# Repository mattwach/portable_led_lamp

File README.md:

# Portable LED Lamp

*The page https://www.instructables.com/Portable-LED-Lamp and [pdf file](Portable-LED-Lamp.pdf)
contain detailed build instructions, a prebuilt firmware (`led_lamp.hex`) file
and prerendered `.stl` files.  The rest of the instructions on this page give
some additional details on the project and to explain how to build your own firmware.*

If you need light but don't have an outlet available, it's nice to have an
efficient light that can accept a wide variety of batteries.

This lamp can accept a wide range of voltages - between 6 and 30V. This allows
it to be **used with different batteries you may have lying around**, including
18650 packs, RC batteries, 12V lead acid, etc.

The unit is designed to be **very efficient** and puts out very little heat, even
at full power. A dimmer knob can be used to adjust the power consumption and
light output. When "off" the lamp consumes less than 40 uA of power in its
"sleep" state.

**Voltage and current are monitored on a small OLED display**. This allows you to
estimate battery life at a given light level and make adjustments as needed for
your situation.

The device has **automatic shutoff when the battery voltage gets too low**.

The device can autodetect the battery you are using with options for manual
override.

Before we get too far, a **disclaimer**:

**Using batteries carries a risk**. Making mistakes can lead to batteries catching
on fire. Sometimes batteries catch on fire even when everything is done
correctly due to unknown issues during manufacturing or shipping. It is
expected that you understand the risks associated with the battery you choose.
Even though the hardware and software in on this page have been tested, you
should not assume that your build and batteries will operate without problems.
I take no responsibility for issues you may encounter while following this
guide or using the provided software. Using a safety container for your battery
is recommended.

# Project Overview

This project contains:

  * Firmware in the `firmware/` directory.  This firmware is intended for the
    ATMega328p running at 3.3v and 8Mhz.  A 3.3V Arduino Pro Mini meets these specs
  * A [KiCad](https://www.kicad.org/) schematic and PCB layout in the
    `schematic/` directory
  * An [OpenSCAD](https://openscad.org/) 3D printable enclosure in the
    `3d_print/` directory.

# Schematics and Images

You'll want the free KiCAD tool to work on the schematics.  The images below are
screen captures from KiCAD for quick reference.

#### Master Board Schematic

#### Input Board Schematic

# Building the firmware

You will need the following commandline tools available.  All are free tools.
Getting them will vary depending on your operating system.

  * `avr-gcc`
  * `avr-objcopy`
  * `avrdude`

To build you run

    make

from the `firmware/` directory.  To upload to a ATMega328p (pro mini) you run

    make upload

Note that upload is currently not setup for windows, although it could be made
to work with a few tweaks to the relatively-simple `rules.mak` file.  The main
issue is likely to be incorrect `avrdude` parameters.  See the main `avrdude`
documentation for for more information.

# Enclosure (using OpenSCAD)

The file `3d_print/led_lamp.scad` contains the 3D models.

At the bottom of the file is a section:

    placed_master_pcb();
    placed_input_pcb();
    placed_picobuck_mount_plate(add_picobucks=true);
    placed_barrel_connector();
    lamp_base();
    placed_led_dome(show_leds=true, barrel_connector_cutout=true);
    input_holder();
    placed_dimmer_knob();

You can place a `*` character or comment out a line with a `//` to omit the
part.  You can also prefix a line with `!` to only show that part.  This is
useful for isolating a part for making a `.stl` model for printing.

# Design Notes

In have [design notes](DESIGN_NOTES.md) where I share test results for LED
efficiency, component power usage and other considerations.

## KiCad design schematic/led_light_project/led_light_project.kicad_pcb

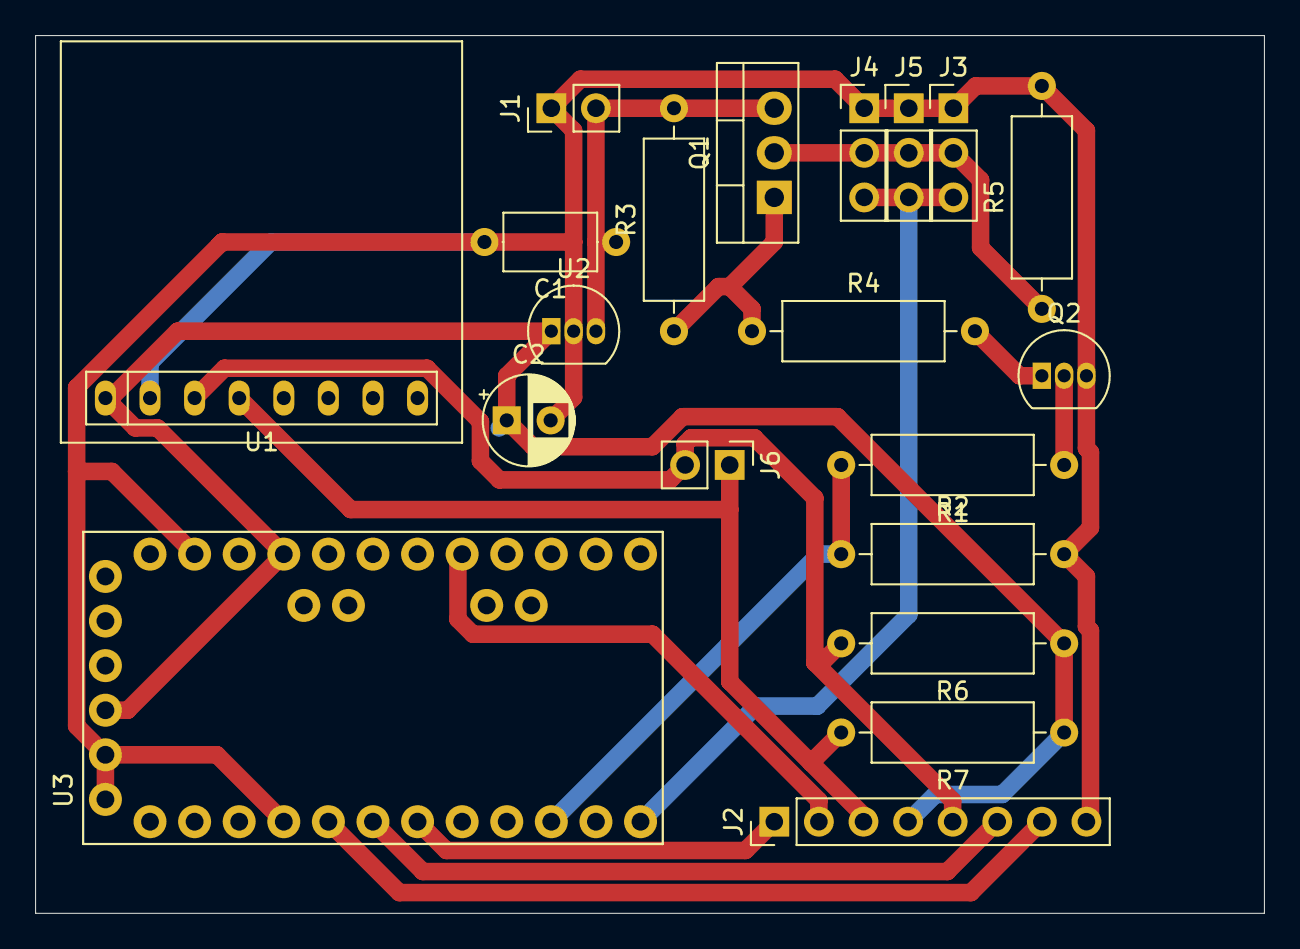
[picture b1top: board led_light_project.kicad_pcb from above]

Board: 2 copper layers, 70.0 x 50.0 mm, 20 parts (0 on the bottom side), 15 nets.

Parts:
C1: 100n; C_Axial_L5.1mm_D3.1mm_P7.50mm_Horizontal
C2: 10u; CP_Radial_D5.0mm_P2.50mm
J1: PWR_IN; PinHeader_1x02_P2.54mm_Vertical
J2: control_board_conn; PinHeader_1x08_P2.54mm_Vertical
J3: PICO_BUCK1; PinHeader_1x03_P2.54mm_Vertical
J4: PICO_BUCK2; PinHeader_1x03_P2.54mm_Vertical
J5: PICO_BUCK3; PinHeader_1x03_P2.54mm_Vertical
J6: I2C_Hookup; PinHeader_1x02_P2.54mm_Vertical
Q1: FQP27P06; TO-220-3_Vertical
Q2: BS170; TO-92_Inline
R1: 1k; R_Axial_DIN0309_L9.0mm_D3.2mm_P12.70mm_Horizontal
R2, R3, R5: 47k; R_Axial_DIN0309_L9.0mm_D3.2mm_P12.70mm_Horizontal
R4: 10k; R_Axial_DIN0309_L9.0mm_D3.2mm_P12.70mm_Horizontal
R6, R7: 4.7k; R_Axial_DIN0309_L9.0mm_D3.2mm_P12.70mm_Horizontal
U1: INA260; Adadruit_INA260_Breakout_Board
U2: LM2936-3.3_TO92; TO-92_Inline
U3: ARDUINO_PRO_MINI; MODULE_ARDUINO_PRO_MINI

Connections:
+3V3: C2.1, J2.4, R6.1, R7.1, U1.10, U2.1, U3.JP1_4, U3.JP6_4
+28V: C1.1, J1.2, Q1.3, R3.2, U2.3
/GREEN_BUT: J2.6, U3.JP7_7
/LED_ON: R1.2, R2.1, U3.JP7_3
/LED_VCC: J3.2, J4.2, J5.2, Q1.2, R5.1
/POTIN: J2.2, U3.JP6_8
/POT_VCC: J2.1, U3.JP7_6
/PWM: J3.3, J4.3, J5.3, U3.JP7_1
/RED_BUT: J2.7, U3.JP7_8
/SCL: J2.5, J6.2, R6.2, U1.9
/SDA: J2.3, J6.1, R7.2, U1.8
GND: C1.2, C2.2, J1.1, J2.8, J3.1, J4.1, J5.1, Q2.3, R2.2, R5.2, U1.6, U2.2, U3.JP1_5, U3.JP1_6, U3.JP6_2, U3.JP7_9
unnamed: Q1.1, R3.1, R4.1
unnamed: Q2.1, R4.2
unnamed: Q2.2, R1.1

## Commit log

2021-08-31 Initial revision.
2021-09-02 Added design notes.
2021-09-02 fixed typo
2021-09-02 Updated intro
2021-09-02 Added instructables link and pdf file.
